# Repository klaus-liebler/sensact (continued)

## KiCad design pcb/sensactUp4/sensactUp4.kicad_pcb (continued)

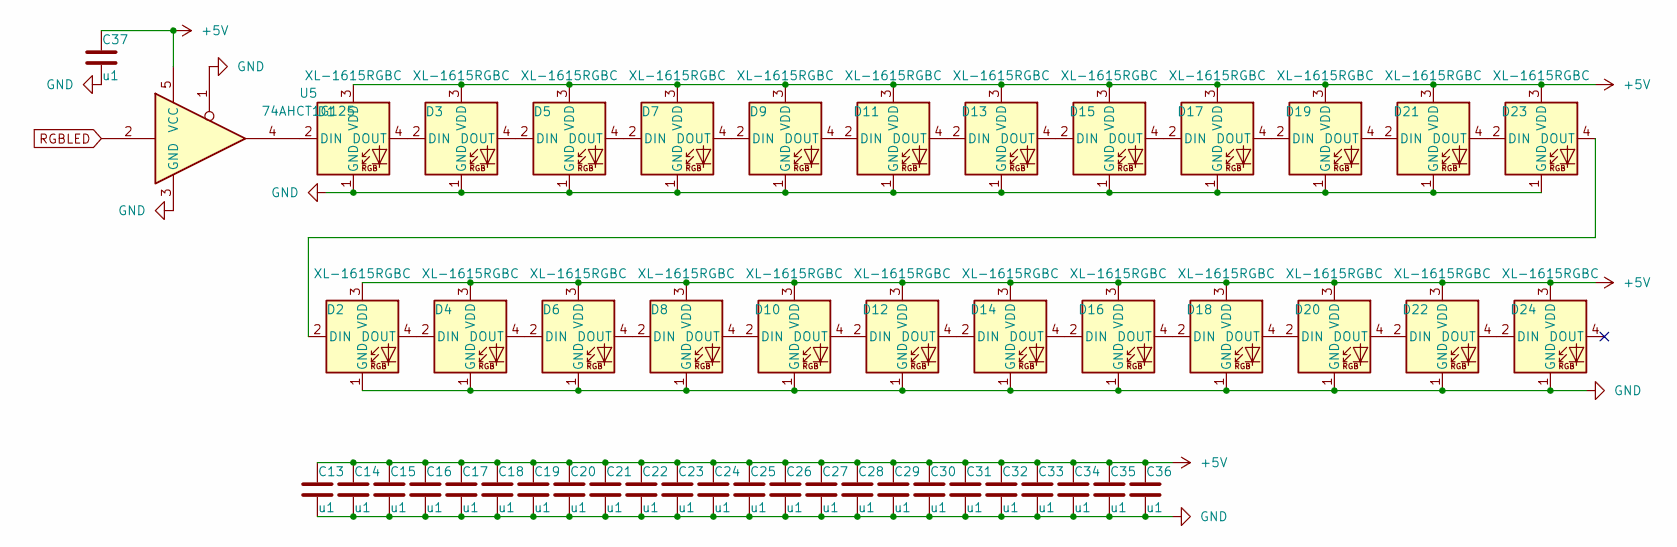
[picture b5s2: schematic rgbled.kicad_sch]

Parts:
C13, C14, C15, C16, C17, C18, C19, C20, C21, C22, C23, C24, C25, C26, C27, C28, C29, C30, C31, C32, C33, C34, C35, C36, C37: u1; C_0201_0603Metric
D1, D2, D3, D4, D5, D6, D7, D8, D9, D10, D11, D12, D13, D14, D15, D16, D17, D18, D19, D20, D21, D22, D23, D24: XL-1615RGBC; XL-1615
U5: 74AHCT1G125; SOT-23-5

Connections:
+5V: C13.1, C14.1, C15.1, C16.1, C17.1, C18.1, C19.1, C20.1, C21.1, C22.1, C23.1, C24.1, C25.1, C26.1, C27.1, C28.1, C29.1, C30.1, C31.1, C32.1, C33.1, C34.1, C35.1, C36.1, C37.1, D1.3 (VDD), D2.3 (VDD), D3.3 (VDD), D4.3 (VDD), D5.3 (VDD), D6.3 (VDD), D7.3 (VDD), D8.3 (VDD), D9.3 (VDD), D10.3 (VDD), D11.3 (VDD), D12.3 (VDD), D13.3 (VDD), D14.3 (VDD), D15.3 (VDD), D16.3 (VDD), D17.3 (VDD), D18.3 (VDD), D19.3 (VDD), D20.3 (VDD), D21.3 (VDD), D22.3 (VDD), D23.3 (VDD), D24.3 (VDD), U5.5 (VCC); also elsewhere on the board
GND: C13.2, C14.2, C15.2, C16.2, C17.2, C18.2, C19.2, C20.2, C21.2, C22.2, C23.2, C24.2, C25.2, C26.2, C27.2, C28.2, C29.2, C30.2, C31.2, C32.2, C33.2, C34.2, C35.2, C36.2, C37.2, D1.1 (GND), D2.1 (GND), D3.1 (GND), D4.1 (GND), D5.1 (GND), D6.1 (GND), D7.1 (GND), D8.1 (GND), D9.1 (GND), D10.1 (GND), D11.1 (GND), D12.1 (GND), D13.1 (GND), D14.1 (GND), D15.1 (GND), D16.1 (GND), D17.1 (GND), D18.1 (GND), D19.1 (GND), D20.1 (GND), D21.1 (GND), D22.1 (GND), D23.1 (GND), D24.1 (GND), U5.1, U5.3 (GND); also elsewhere on the board
unnamed: D1.2 (DIN), U5.4
unnamed: D1.4 (DOUT), D3.2 (DIN)
unnamed: D2.2 (DIN), D23.4 (DOUT)
unnamed: D2.4 (DOUT), D4.2 (DIN)
unnamed: D3.4 (DOUT), D5.2 (DIN)
unnamed: D4.4 (DOUT), D6.2 (DIN)
unnamed: D5.4 (DOUT), D7.2 (DIN)
unnamed: D6.4 (DOUT), D8.2 (DIN)
unnamed: D7.4 (DOUT), D9.2 (DIN)
unnamed: D8.4 (DOUT), D10.2 (DIN)
unnamed: D10.4 (DOUT), D12.2 (DIN)
unnamed: D9.4 (DOUT), D11.2 (DIN)
unnamed: D11.4 (DOUT), D13.2 (DIN)
unnamed: D12.4 (DOUT), D14.2 (DIN)
unnamed: D13.4 (DOUT), D15.2 (DIN)
unnamed: D14.4 (DOUT), D16.2 (DIN)
unnamed: D15.4 (DOUT), D17.2 (DIN)
unnamed: D16.4 (DOUT), D18.2 (DIN)
unnamed: D17.4 (DOUT), D19.2 (DIN)
unnamed: D18.4 (DOUT), D20.2 (DIN)
unnamed: D19.4 (DOUT), D21.2 (DIN)
unnamed: D20.4 (DOUT), D22.2 (DIN)
unnamed: D21.4 (DOUT), D23.2 (DIN)
unnamed: D22.4 (DOUT), D24.2 (DIN)
RGBLED: U5.2; also elsewhere on the board

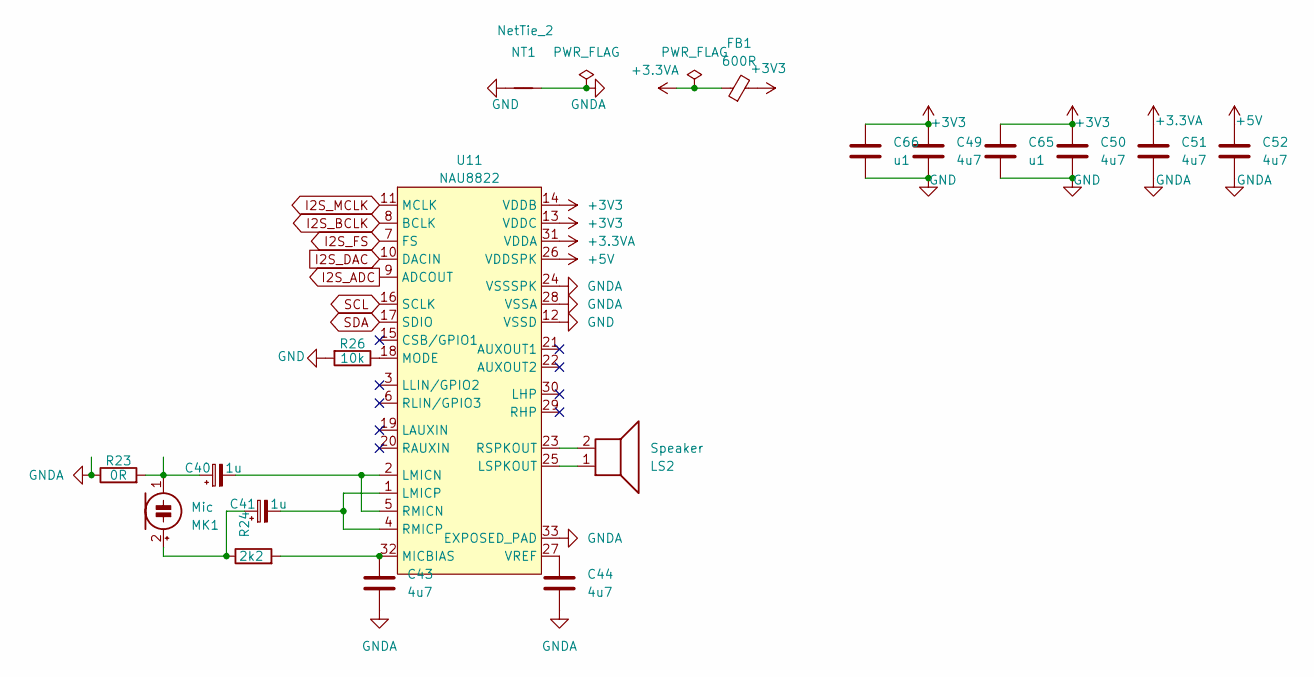
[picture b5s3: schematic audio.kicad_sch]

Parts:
C40, C41: 1u; CP_EIA-3216-10_Kemet-I; MPN TAJA105K016RNJ
C43, C44, C49, C50, C51, C52: 4u7; C_0402_1005Metric; MPN CL05A475MP5NRNC
C65, C66: u1; C_0201_0603Metric; MPN GRM033R61A104KE15D
FB1: 600R; L_0603_1608Metric; MPN BLM18AG601SN1D
LS2: Speaker; PinHeader_1x02_P1.27mm_Vertical
MK1: Mic; Microphone_6mm; MPN GMI6050P-64DB
NT1: NetTie_2; NetTie-2_SMD_Pad0.5mm
R23: 0R; R_0805_2012Metric_Pad1.20x1.40mm_HandSolder; MPN 0805W8F0000T5E
R24: 2k2; R_0402_1005Metric; MPN 0402WGF2201TCE
R26: 10k; R_0201_0603Metric; MPN 0201WMF1002TEE
U11: NAU8822; QFN-32-1EP_5x5mm_P0.5mm_EP3.6x3.6mm_ThermalVias; MPN NAU88C22YG

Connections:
+3.3VA: C51.1, FB1.1, U11.31 (VDDA)
+3V3: C49.1, C50.1, C65.1, C66.1, FB1.2, U11.13 (VDDC), U11.14 (VDDB); also elsewhere on the board
+5V: C52.1, U11.26 (VDDSPK); also elsewhere on the board
GND: C49.2, C50.2, C65.2, C66.2, NT1.1, R26.2, U11.12 (VSSD); also elsewhere on the board
GNDA: C43.2, C44.2, C51.2, C52.2, NT1.2, R23.1, U11.24 (VSSSPK), U11.28 (VSSA), U11.33 (EXPOSED_PAD)
I2S_ADC: U11.9 (ADCOUT); also elsewhere on the board
I2S_BCLK: U11.8 (BCLK); also elsewhere on the board
I2S_DAC: U11.10 (DACIN); also elsewhere on the board
I2S_FS: U11.7 (FS); also elsewhere on the board
I2S_MCLK: U11.11 (MCLK); also elsewhere on the board
unnamed: C41.1, MK1.2 (+), R24.1
unnamed: C40.1, MK1.1 (-), R23.2
unnamed: C40.2, U11.2 (LMICN), U11.5 (RMICN)
unnamed: C41.2, U11.1 (LMICP), U11.4 (RMICP)
unnamed: LS2.1, U11.25 (LSPKOUT)
unnamed: C43.1, R24.2, U11.32 (MICBIAS)
unnamed: R26.1, U11.18 (MODE)
unnamed: LS2.2, U11.23 (RSPKOUT)
unnamed: C44.1, U11.27 (VREF)
SCL: U11.16 (SCLK); also elsewhere on the board
SDA: U11.17 (SDIO); also elsewhere on the board

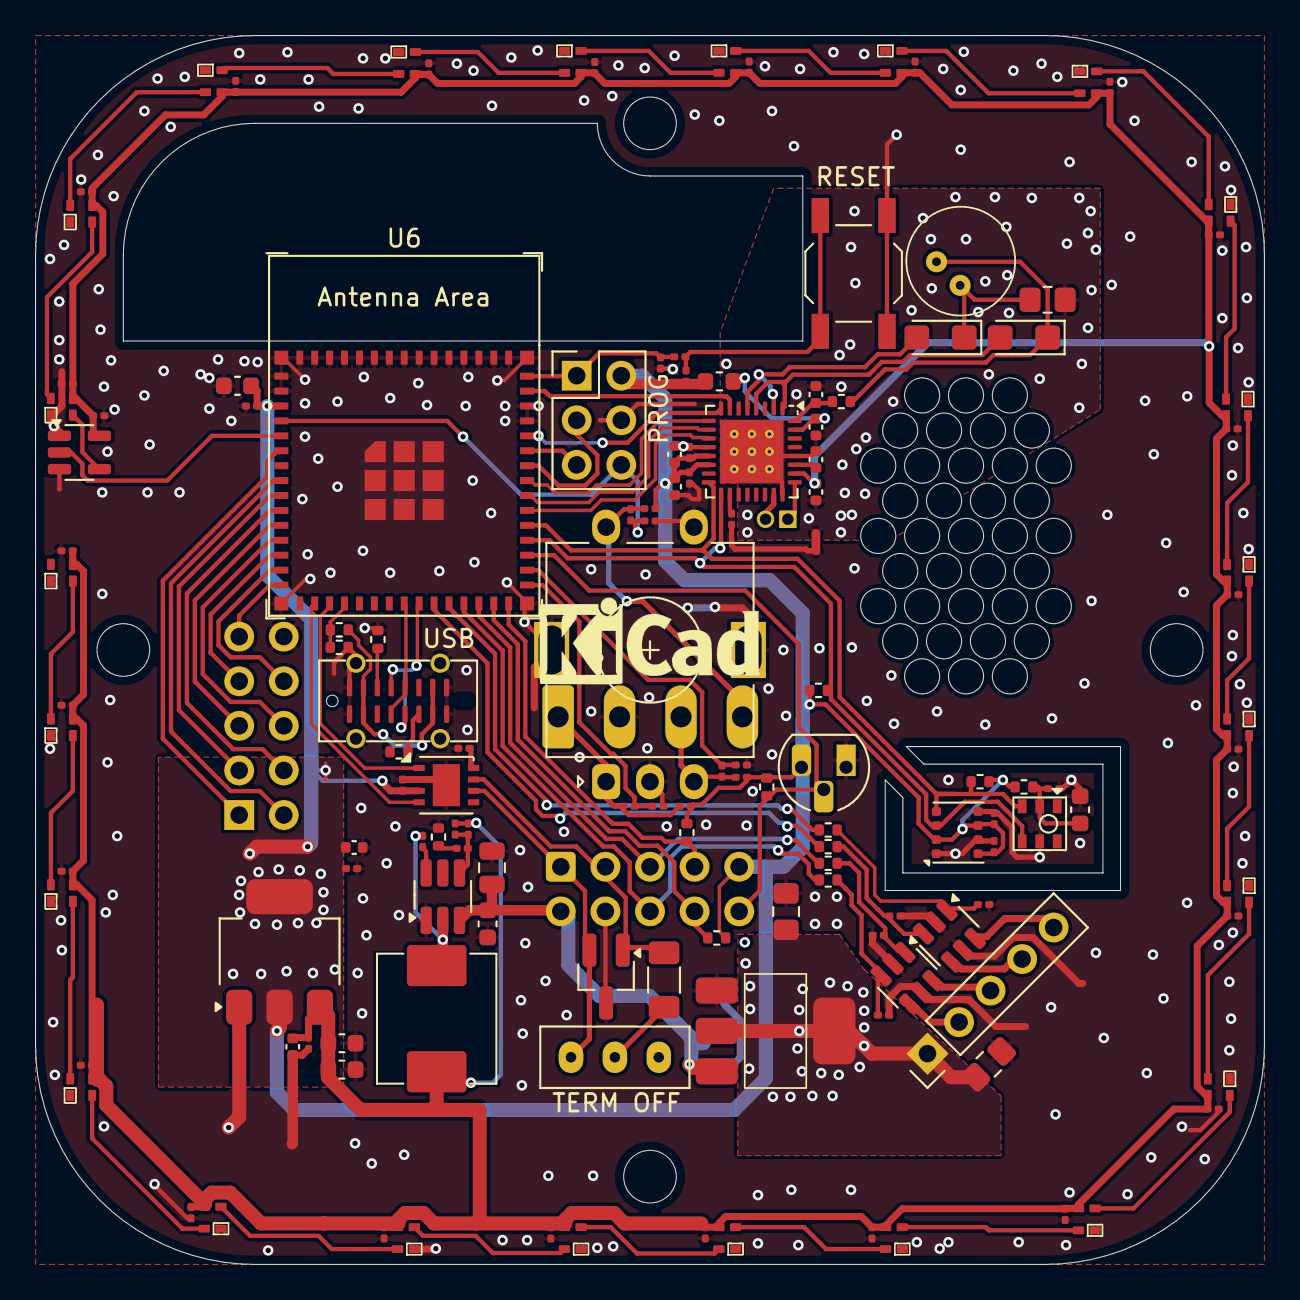
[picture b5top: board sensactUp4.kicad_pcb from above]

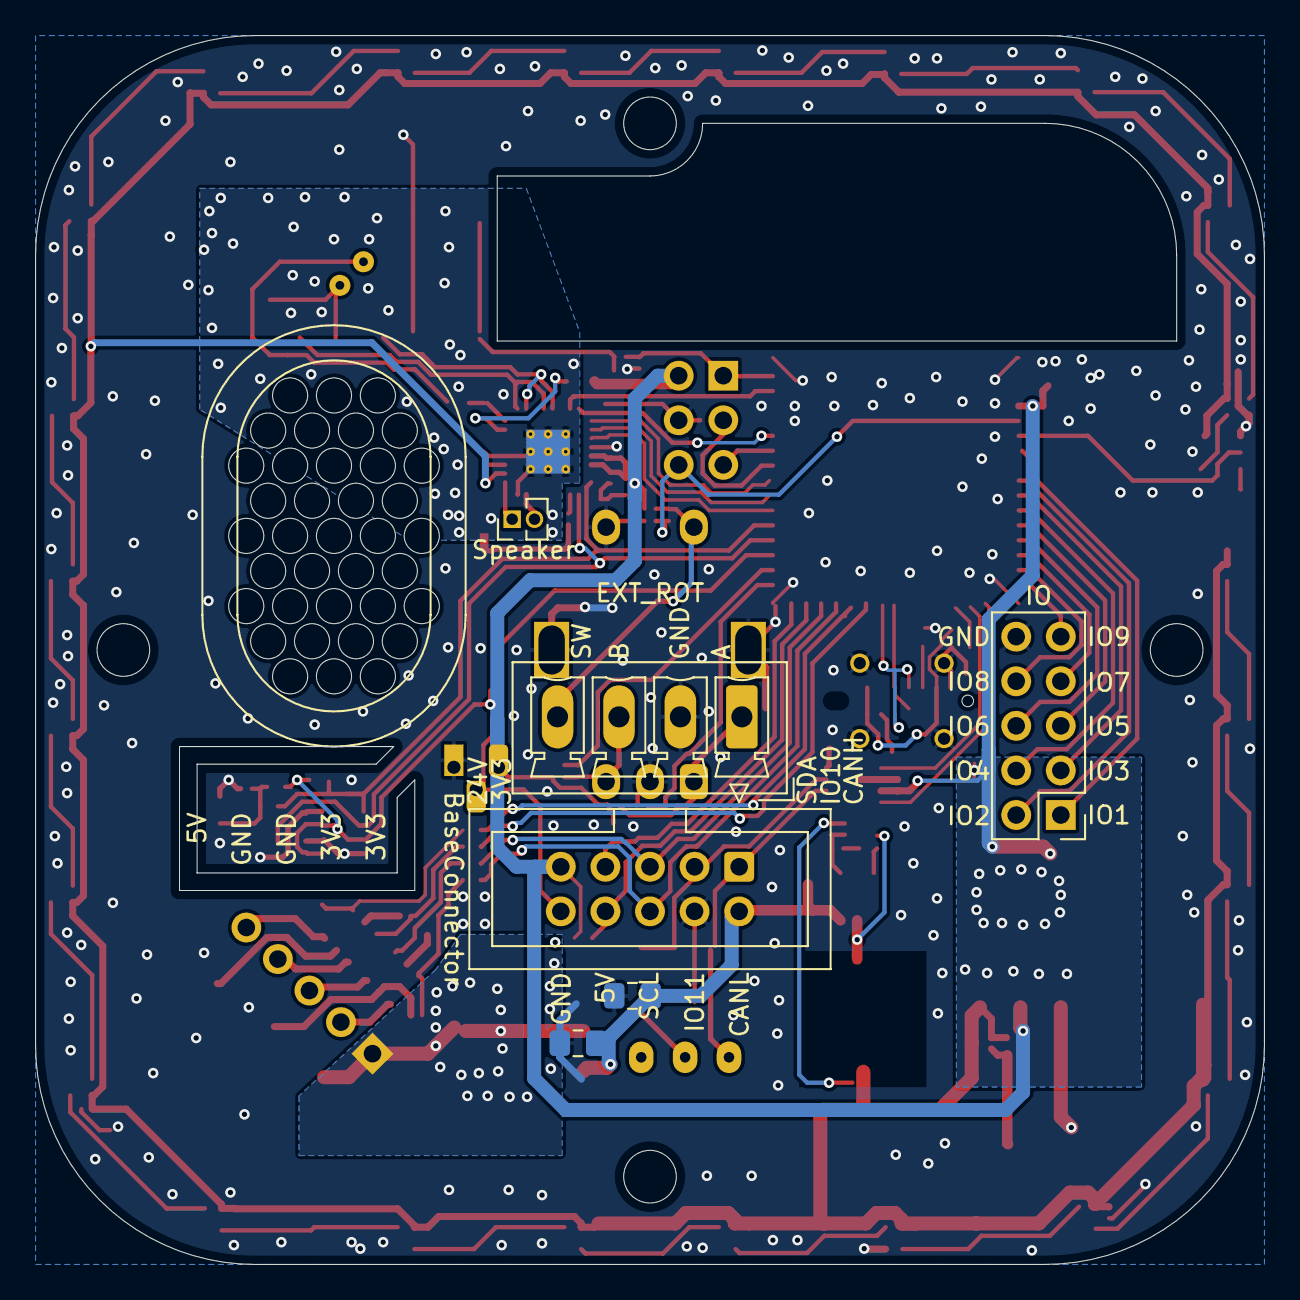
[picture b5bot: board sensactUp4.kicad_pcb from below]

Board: 2 copper layers, 70.0 x 70.0 mm, 147 parts (7 on the bottom side), 99 nets.

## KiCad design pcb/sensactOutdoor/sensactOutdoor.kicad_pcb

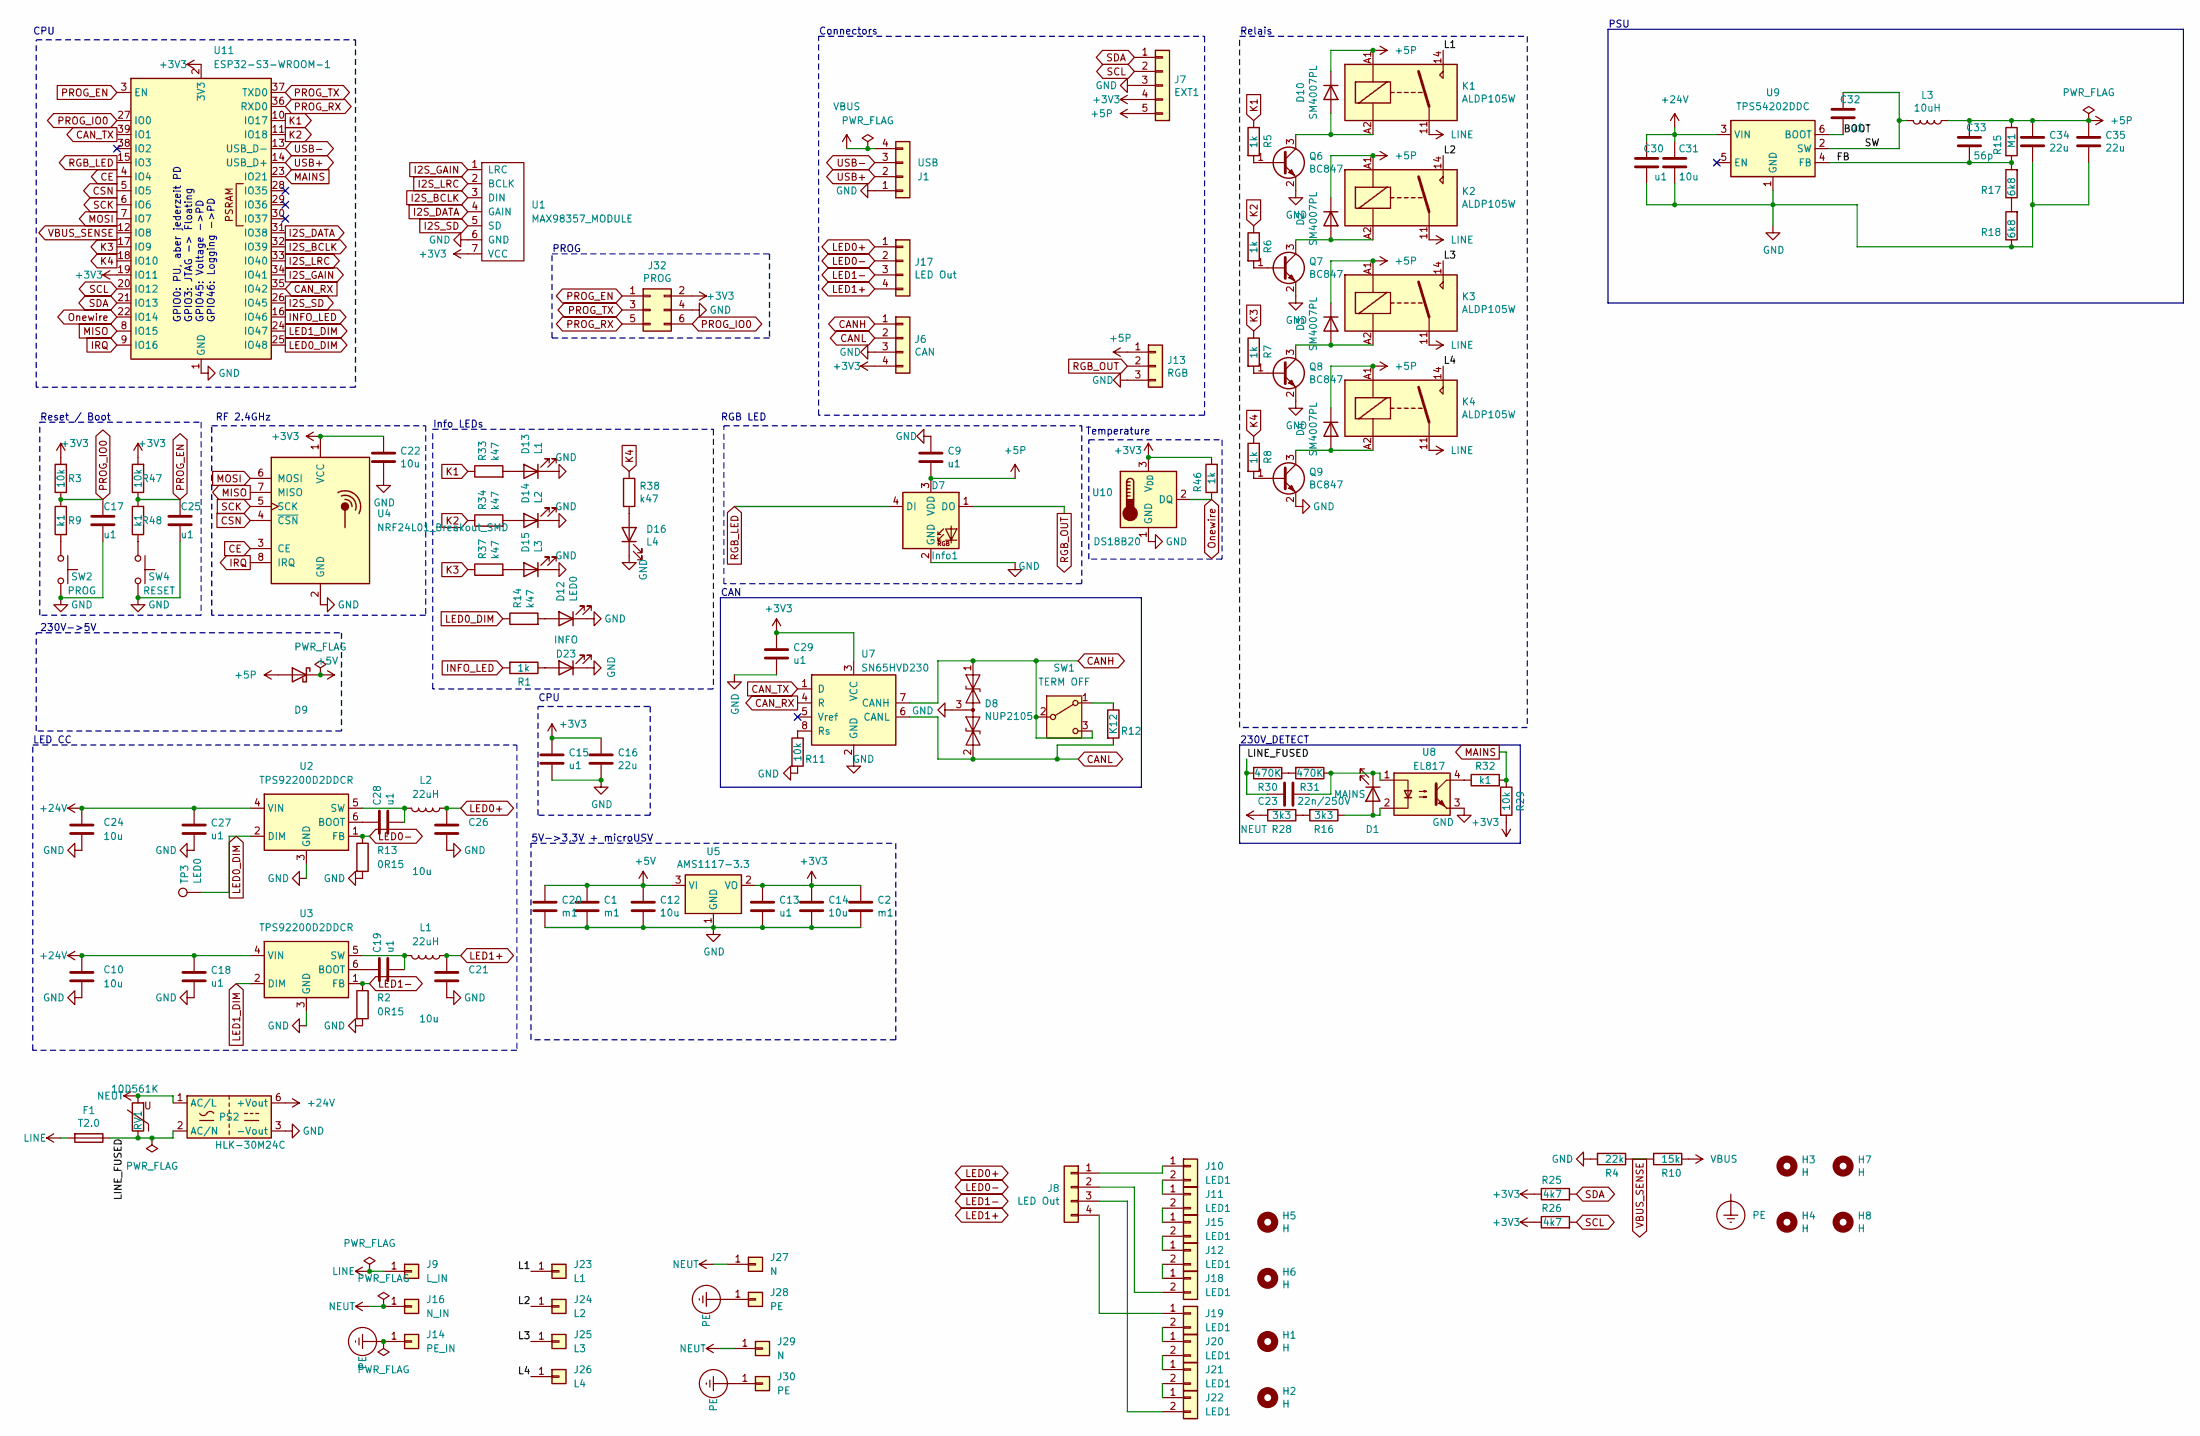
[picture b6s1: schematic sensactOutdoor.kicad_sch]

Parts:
C1, C2, C20: m1; C_1206_3216Metric; JLCPCB C15008
C9, C13, C17, C18, C19, C25, C27, C28, C30, C32: u1; C_0805_2012Metric_Pad1.18x1.45mm_HandSolder
C10, C21, C24, C26, C31: 10u; C_1206_3216Metric_Pad1.33x1.80mm_HandSolder
C12: 10u; C_0805_2012Metric_Pad1.18x1.45mm_HandSolder; JLCPCB C19702
C14, C22: 10u; C_0805_2012Metric_Pad1.18x1.45mm_HandSolder
C15: u1; C_0805_2012Metric_Pad1.18x1.45mm_HandSolder; JLCPCB C1525
C16: 22u; C_0805_2012Metric_Pad1.18x1.45mm_HandSolder; JLCPCB C59461
C23: 22n/250V; C_Rect_L11.0mm_W5.1mm_P10.00mm_MKT
C29: u1; C_0805_2012Metric; MPN GRM033R61A104KE15D
C33: 56p; C_0805_2012Metric_Pad1.18x1.45mm_HandSolder
C34, C35: 22u; C_0805_2012Metric_Pad1.18x1.45mm_HandSolder
D1: MAINS; LED_0805_2012Metric_Pad1.15x1.40mm_HandSolder
D2, D3, D4, D10: SM4007PL; D_SOD-123_handsolder; JLCPCB C64898
D7: Info1; LED_D5.0mm-4_RGB_Staggered_Pins
D8: NUP2105; SOT-23_Handsoldering; MPN NUP2105L
D9: 1N5819WS; D_SMA_Handsoldering
D12: LED0; LED_0805_2012Metric_Pad1.15x1.40mm_HandSolder; JLCPCB C2286
D13: L1; LED_0805_2012Metric_Pad1.15x1.40mm_HandSolder; JLCPCB C2286
D14: L2; LED_0805_2012Metric_Pad1.15x1.40mm_HandSolder; JLCPCB C2286
D15: L3; LED_0805_2012Metric_Pad1.15x1.40mm_HandSolder; JLCPCB C2286
D16: L4; LED_0805_2012Metric_Pad1.15x1.40mm_HandSolder; JLCPCB C2286
D23: INFO; LED_0805_2012Metric_Pad1.15x1.40mm_HandSolder
F1: T2.0; Fuse_Littelfuse_372_D8.50mm
H1, H2, H3, H4, H5, H6, H7, H8: H; MountingHole_3.2mm_M3
J1: USB; PinHeader_1x04_P2.54mm_Vertical
J6: CAN; PhoenixContact_MCV_1,5_4-G-3.5_1x04_P3.50mm_Vertical
J7: EXT1; JST_XH_B5B-XH-A_1x05_P2.50mm_Vertical
J8: LED Out; ÖLFLEX 4x1mm2
J9: L_IN; Flachstecker gewinkelt 4,8 oder 6,35mm
J10, J11, J12, J15, J18, J19, J20, J21, J22: LED1; JST_XH_B2B-XH-A_1x02_P2.50mm_Vertical
J13: RGB; PinHeader_1x03_P2.54mm_Vertical
J14: PE_IN; Flachstecker gewinkelt 4,8 oder 6,35mm
J16: N_IN; Flachstecker gewinkelt 4,8 oder 6,35mm
J17: LED Out; PhoenixContact_MCV_1,5_4-G-3.5_1x04_P3.50mm_Vertical
J23: L1; Flachstecker gewinkelt 4,8 oder 6,35mm
J24: L2; Flachstecker gewinkelt 4,8 oder 6,35mm
J25: L3; Flachstecker gewinkelt 4,8 oder 6,35mm
J26: L4; Flachstecker gewinkelt 4,8 oder 6,35mm
J27, J29: N; Flachstecker gewinkelt 4,8 oder 6,35mm
J28, J30: PE; Flachstecker gewinkelt 4,8 oder 6,35mm
J32: PROG; PinHeader_2x03_P2.54mm_Vertical
K1, K2, K3, K4: ALDP105W; RELAY_ALDP105W
L1, L2: 22uH; L_0630; JLCPCB C408455
L3: 10uH; L_0630
PS2: HLK-30M24C; Converter_ACDC_Hi-Link_HLK-30Mxx
Q6: BC847; SOT-23_Handsoldering; JLCPCB C8512
Q7, Q8, Q9: BC847; SOT-23_Handsoldering
R1, R5, R6, R7, R8, R46: 1k; R_0805_2012Metric_Pad1.20x1.40mm_HandSolder
R2, R13: 0R15; R_1206_3216Metric_Pad1.30x1.75mm_HandSolder; JLCPCB C25271
R3, R29, R47: 10k; R_0805_2012Metric_Pad1.20x1.40mm_HandSolder
R4: 22k; R_0805_2012Metric_Pad1.20x1.40mm_HandSolder
R9, R32, R48: k1; R_0805_2012Metric_Pad1.20x1.40mm_HandSolder
R10: 15k; R_0805_2012Metric_Pad1.20x1.40mm_HandSolder
R11: 10k; R_0805_2012Metric_Pad1.20x1.40mm_HandSolder; MPN 0201WMF1002TEE
R12: K12; R_1206_3216Metric_Pad1.30x1.75mm_HandSolder; MPN 1206W4F1200T5E
R14, R33, R34, R37, R38: k47; R_0805_2012Metric_Pad1.20x1.40mm_HandSolder
R15: M1; R_0805_2012Metric_Pad1.20x1.40mm_HandSolder
R16, R28: 3k3; R_2512_6332Metric_Pad1.40x3.35mm_HandSolder
R17, R18: 6k8; R_0805_2012Metric_Pad1.20x1.40mm_HandSolder
R25, R26: 4k7; R_0805_2012Metric_Pad1.20x1.40mm_HandSolder
R30, R31: 470K; R_2512_6332Metric_Pad1.40x3.35mm_HandSolder
RV1: 10D561K; RV_Disc_D12mm_W3.9mm_P7.5mm
SW1: TERM OFF; Switch_SS12D00
SW2: PROG; SW_SPST_TL3342_smaller_handsolder
SW4: RESET; SW_SPST_TL3342_smaller_handsolder
TP3: LED0; TestPoint_THTPad_D2.0mm_Drill1.0mm
U1: MAX98357_MODULE; PinHeader_1x07_P2.54mm_Vertical
U2, U3: TPS92200D2DDCR; SOT-23-6_Handsoldering
U4: NRF24L01_Breakout_SMD; NRF24L01-Module-SMD
U5: AMS1117-3.3; SOT-223-3_TabPin2_HANDSOLDER
U7: SN65HVD230; SOIC-8_3.9x4.9mm_Pitch1.27mm_handsolder; MPN SN65HVD230DR
U8: EL817; SO-4_7.6x3.6mm_P2.54mm_handsolder
U9: TPS54202DDC; SOT-23-6_Handsoldering
U10: DS18B20; TO-92L_HandSolder
U11: ESP32-S3-WROOM-1; ESP32-S3-WROOM-1_handsolder

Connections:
+3V3: C2.1, C13.1, C14.1, C15.1, C16.1, C22.1, C29.1, J6.4, J7.4, J32.2, R3.2, R25.1, R26.1, R29.2, R46.2, R47.2, U1.7 (VCC), U4.1 (VCC), U5.2 (VO), U7.3 (VCC), U10.3 (V_{DD}), U11.2 (3V3), U11.19 (IO11)
+5P: C9.2, C33.2, C34.1, C35.1, D2.1 (K), D3.1 (K), D4.1 (K), D7.3 (VDD), D9.2 (A), D10.1 (K), J7.5, J13.1, K1.A1, K2.A1, K3.A1, K4.A1, L3.1, R15.1
+5V: C1.1, C12.1, C20.1, D9.1 (K), U5.3 (VI)
+24V: C10.1, C18.1, C24.1, C27.1, C30.2, C31.2, PS2.6 (+Vout), U2.4 (VIN), U3.4 (VIN), U9.3 (VIN)
/BOOT: C32.1, U9.6 (BOOT)
/FB: C33.1, R15.2, R17.2, U9.4 (FB)
/L1: J23.1, K1.14
/L2: J24.1, K2.14
/L3: J25.1, K3.14
/L4: J26.1, K4.14
/LINE_FUSED: C23.1, F1.1, PS2.2 (AC/N), R30.2, RV1.1
/SW: C32.2, L3.2, U9.2 (SW)
CANH: D8.1 (A1), J6.1, SW1.2 (B), SW1.3 (C), U7.7 (CANH)
CANL: D8.2 (A2), J6.2, R12.2, U7.6 (CANL)
CAN_RX: U7.4 (R), U11.35 (IO42)
CAN_TX: U7.1 (D), U11.39 (IO1)
CE: U4.3 (CE), U11.4 (IO4)
CSN: U4.4 (~CSN), U11.5 (IO5)
GND: C1.2, C2.2, C9.1, C10.2, C12.2, C13.2, C14.2, C15.2, C16.2, C17.2, C18.2, C20.2, C21.2, C22.2, C24.2, C25.2, C26.2, C27.2, C29.2, C30.1, C31.1, C34.2, C35.2, D7.2 (GND), D8.3 (common), D12.1 (K), D13.1 (K), D14.1 (K), D15.1 (K), D16.1 (K), D23.1 (K), J1.1, J6.3, J7.3, J13.3, J32.4, PS2.3 (-Vout), Q6.2 (E), Q7.2 (E), Q8.2 (E), Q9.2 (E), R2.2, R4.2, R11.2, R13.2, R18.1, SW2.2, SW4.2, U1.6 (GND), U2.3 (GND), U3.3 (GND), U4.2 (GND), U5.1 (GND), U7.2 (GND), U8.3, U9.1 (GND), U10.1 (GND), U11.1 (GND), U11.40 (GND), U11.41 (GND)
I2S_BCLK: U1.3 (DIN), U11.32 (IO39)
I2S_DATA: U1.4 (GAIN), U11.31 (IO38)
I2S_GAIN: U1.1 (LRC), U11.34 (IO41)
I2S_LRC: U1.2 (BCLK), U11.33 (IO40)
I2S_SD: U1.5 (SD), U11.26 (IO45)
INFO_LED: R1.2, U11.16 (IO46)
IRQ: U4.8 (IRQ), U11.9 (IO16)
K1: R5.1, R33.1, U11.10 (IO17)
K2: R6.1, R34.1, U11.11 (IO18)
K3: R7.1, R37.1, U11.17 (IO9)
K4: R8.1, R38.1, U11.18 (IO10)
LED0+: C26.1, J17.1, L2.1
LED0-: J17.2, R13.1, U2.1 (FB)
LED0_DIM: R14.1, TP3.1, U2.2 (DIM), U11.25 (IO48)
LED1+: C21.1, J17.4, L1.1
LED1-: J17.3, R2.1, U3.1 (FB)
LED1_DIM: U3.2 (DIM), U11.24 (IO47)
LINE: F1.2, J9.1, K1.11, K2.11, K3.11, K4.11
MAINS: R29.1, R32.2, U11.23 (IO21)
MISO: U4.7 (MISO), U11.8 (IO15)
MOSI: U4.6 (MOSI), U11.7 (IO7)
NEUT: J16.1, J27.1, J29.1, PS2.1 (AC/L), R28.2, RV1.2
unnamed: D1.2 (A), R16.1, U8.2
unnamed: C23.2, D1.1 (K), R31.1, U8.1
unnamed: D2.2 (A), K2.A2, Q7.3 (C)
unnamed: D3.2 (A), K3.A2, Q8.3 (C)
unnamed: D4.2 (A), K4.A2, Q9.3 (C)
unnamed: D10.2 (A), K1.A2, Q6.3 (C)
unnamed: D12.2 (A), R14.2
unnamed: D13.2 (A), R33.2
unnamed: D14.2 (A), R34.2
unnamed: D15.2 (A), R37.2
unnamed: D16.2 (A), R38.2
unnamed: D23.2 (A), R1.1
unnamed: J8.1, J10.1
unnamed: J10.2, J11.1
unnamed: J11.2, J15.1
unnamed: J12.1, J15.2
unnamed: J12.2, J18.1
unnamed: J8.2, J18.2
unnamed: J8.4, J19.1
unnamed: J19.2, J20.1
unnamed: J20.2, J21.1
unnamed: J21.2, J22.1
unnamed: J8.3, J22.2
unnamed: Q6.1 (B), R5.2
unnamed: Q7.1 (B), R6.2
unnamed: Q8.1 (B), R7.2
unnamed: Q9.1 (B), R8.2
unnamed: R9.1, SW2.1
unnamed: R16.2, R28.1
unnamed: R17.1, R18.2
unnamed: R30.1, R31.2
unnamed: R32.1, U8.4
unnamed: R48.1, SW4.1
unnamed: R12.1, SW1.1 (A)
unnamed: C28.1, U2.6 (BOOT)
unnamed: C28.2, L2.2, U2.5 (SW)
unnamed: C19.1, U3.6 (BOOT)
unnamed: C19.2, L1.2, U3.5 (SW)
unnamed: R11.1, U7.8 (Rs)
Onewire: R46.1, U10.2 (DQ), U11.22 (IO14)
PE: J14.1, J28.1, J30.1
PROG_EN: C25.1, J32.1, R47.1, R48.2, U11.3 (EN)
PROG_IO0: C17.1, J32.6, R3.1, R9.2, U11.27 (IO0)
PROG_RX: J32.5, U11.36 (RXD0)
PROG_TX: J32.3, U11.37 (TXD0)
RGB_LED: D7.4 (DI), U11.15 (IO3)
RGB_OUT: D7.1 (DO), J13.2
SCK: U4.5 (SCK), U11.6 (IO6)
SCL: J7.2, R26.2, U11.20 (IO12)
SDA: J7.1, R25.2, U11.21 (IO13)
USB+: J1.2, U11.14 (USB_D+)
USB-: J1.3, U11.13 (USB_D-)
VBUS: J1.4, R10.1
VBUS_SENSE: R4.1, R10.2, U11.12 (IO8)

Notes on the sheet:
230V->5V
Relais
CPU
Temperature
LED CC
PSU
RF 2.4GHz
Connectors
CAN
230V_DETECT
Info LEDs
Reset / Boot
RGB LED
PROG
5V->3,3V + microUSV
GPIO0: PU, aber jederzeit PD GPIO3: JTAG -> Floating GPIO45: Voltage ->PD GPIO46: Logging ->PD

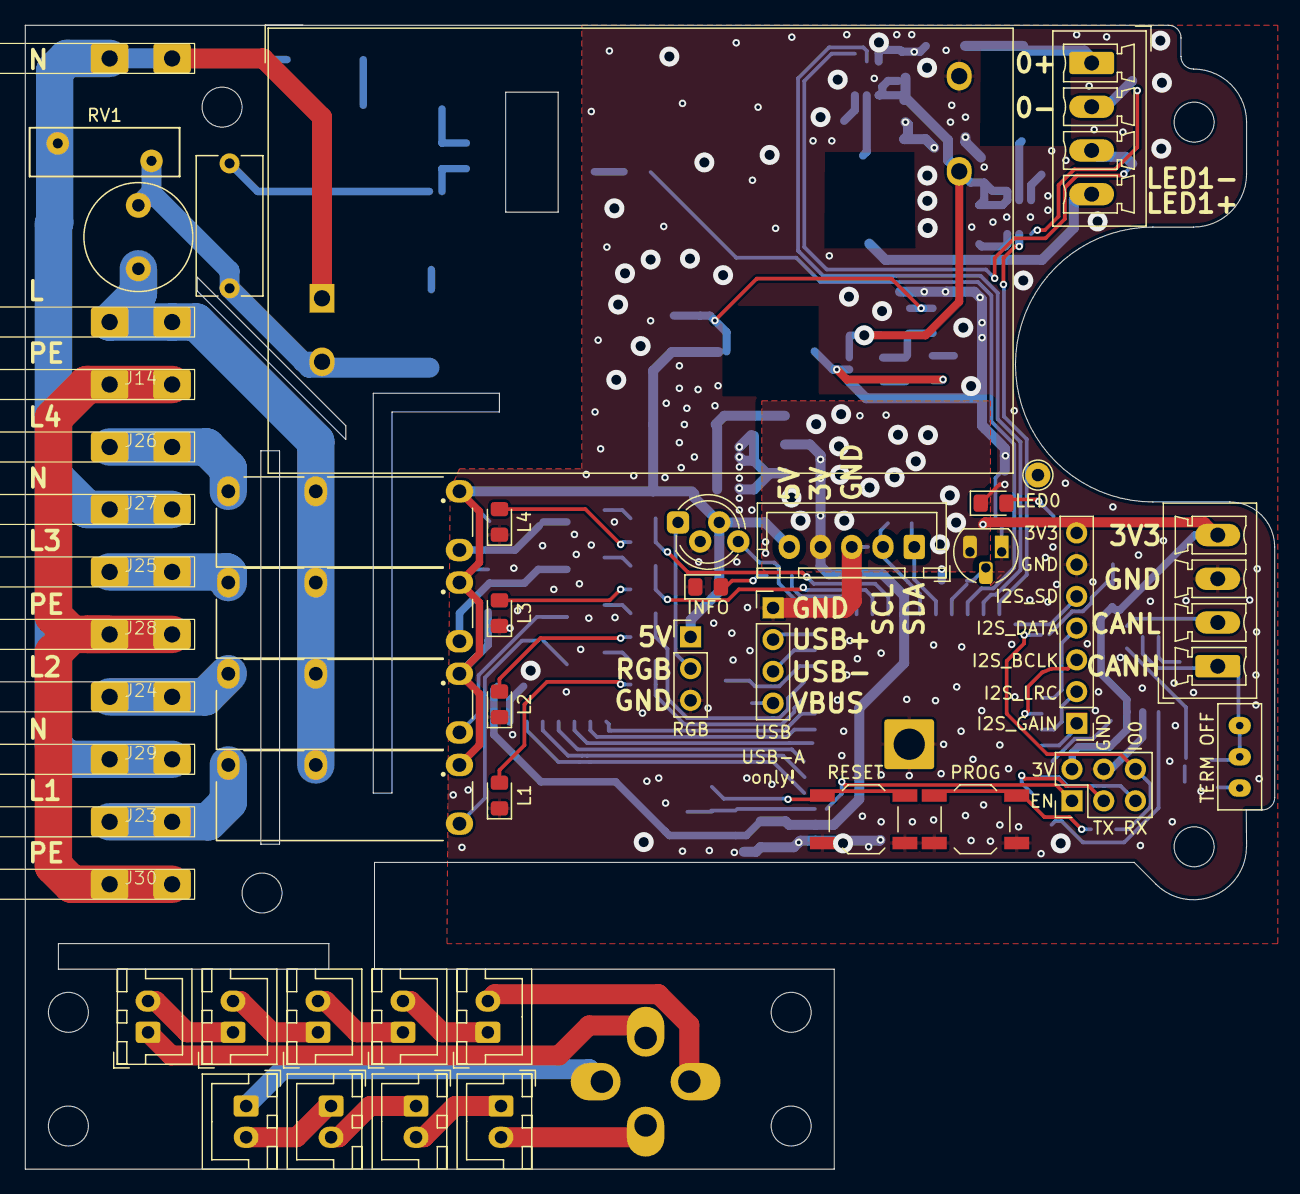
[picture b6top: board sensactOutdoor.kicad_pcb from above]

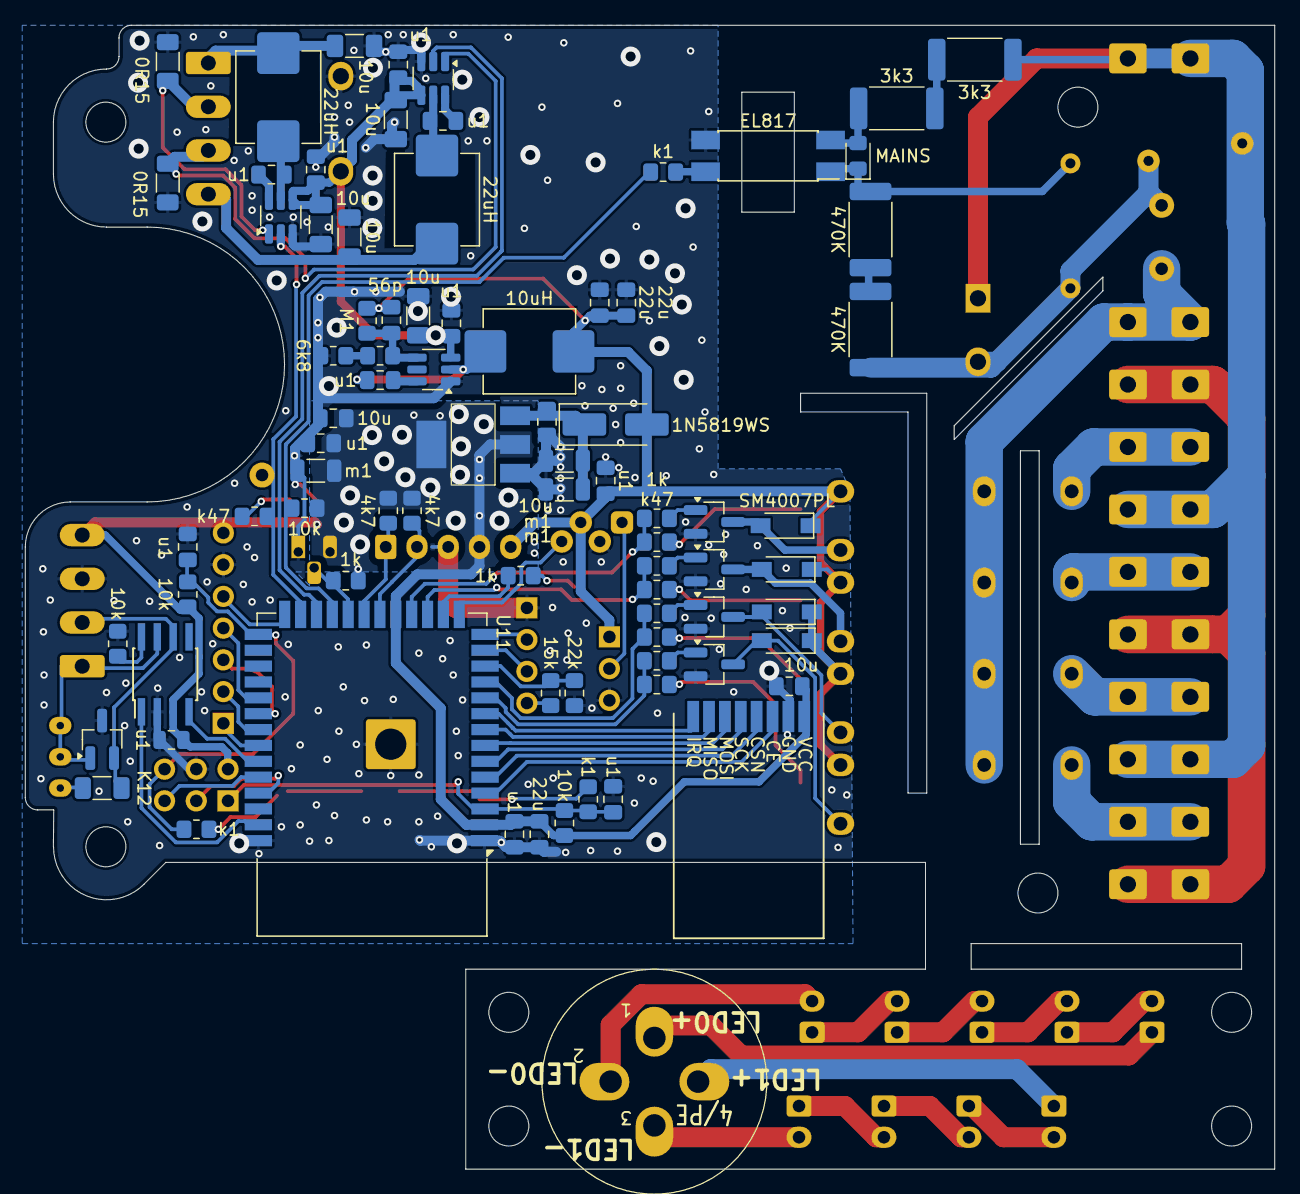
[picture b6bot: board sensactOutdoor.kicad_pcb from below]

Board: 2 copper layers, 100.0 x 91.6 mm, 137 parts (82 on the bottom side), 95 nets.

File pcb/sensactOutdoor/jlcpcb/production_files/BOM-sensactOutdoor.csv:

Comment,Designator,Footprint,LCSC,Quantity
m1,"C1,C2,C20",C_1206_3216Metric,C15008,3
u1,C15,C_0805_2012Metric_Pad1.18x1.45mm_HandSolder,C1525,1
10u,C12,C_0805_2012Metric_Pad1.18x1.45mm_HandSolder,C19702,1
LED0,"D12,D13,D14,D15,D16",LED_0805_2012Metric_Pad1.15x1.40mm_HandSolder,C2286,5
0R15,"R13,R2",R_1206_3216Metric_Pad1.30x1.75mm_HandSolder,C25271,2
22uH,"L1,L2",L_0630,C408455,2
u1,"C13,C17,C18,C19,C25,C27,C28,C30,C32,C9",C_0805_2012Metric_Pad1.18x1.45mm_HandSolder,C49678,10
22u,C16,C_0805_2012Metric_Pad1.18x1.45mm_HandSolder,C59461,1
SM4007PL,"D10,D2,D3,D4",D_SOD-123_handsolder,C64898,4
BC847,Q6,SOT-23_Handsoldering,C8512,1
LED1,J22,JST_XH_B2B-XH-A_1x02_P2.50mm_Vertical,,1
H,H6,MountingHole_3.2mm_M3,,1
L1,J23,"Flachstecker gewinkelt 4,8 oder 6,35mm",,1
LED1,J15,JST_XH_B2B-XH-A_1x02_P2.50mm_Vertical,,1
ALDP105W,K1,RELAY_ALDP105W,,1
H,H1,MountingHole_3.2mm_M3,,1
LED1,J10,JST_XH_B2B-XH-A_1x02_P2.50mm_Vertical,,1
N,J29,"Flachstecker gewinkelt 4,8 oder 6,35mm",,1
LED Out,J17,"PhoenixContact_MCV_1,5_4-G-3.5_1x04_P3.50mm_Vertical",,1
H,H5,MountingHole_3.2mm_M3,,1
INFO,D23,LED_0805_2012Metric_Pad1.15x1.40mm_HandSolder,,1
RGB,J13,PinHeader_1x03_P2.54mm_Vertical,,1
DS18B20,U10,TO-92L_HandSolder,,1
LED1,J19,JST_XH_B2B-XH-A_1x02_P2.50mm_Vertical,,1
LED0,TP3,TestPoint_THTPad_D2.0mm_Drill1.0mm,,1
10D561K,RV1,RV_Disc_D12mm_W3.9mm_P7.5mm,,1
N,J27,"Flachstecker gewinkelt 4,8 oder 6,35mm",,1
L_IN,J9,"Flachstecker gewinkelt 4,8 oder 6,35mm",,1
T2.0,F1,Fuse_Littelfuse_372_D8.50mm,,1
MAX98357_MODULE,U1,PinHeader_1x07_P2.54mm_Vertical,,1
LED1,J12,JST_XH_B2B-XH-A_1x02_P2.50mm_Vertical,,1
PE,J28,"Flachstecker gewinkelt 4,8 oder 6,35mm",,1
H,H8,MountingHole_3.2mm_M3,,1
L3,J25,"Flachstecker gewinkelt 4,8 oder 6,35mm",,1
ALDP105W,K2,RELAY_ALDP105W,,1
N_IN,J16,"Flachstecker gewinkelt 4,8 oder 6,35mm",,1
LED1,J11,JST_XH_B2B-XH-A_1x02_P2.50mm_Vertical,,1
PROG,SW2,SW_SPST_TL3342_smaller_handsolder,,1
LED1,J20,JST_XH_B2B-XH-A_1x02_P2.50mm_Vertical,,1
USB,J1,PinHeader_1x04_P2.54mm_Vertical,,1
22n/250V,C23,C_Rect_L11.0mm_W5.1mm_P10.00mm_MKT,,1
H,H3,MountingHole_3.2mm_M3,,1
TERM OFF,SW1,Switch_SS12D00,,1
PROG,J32,PinHeader_2x03_P2.54mm_Vertical,,1
ALDP105W,K4,RELAY_ALDP105W,,1
RESET,SW4,SW_SPST_TL3342_smaller_handsolder,,1
L4,J26,"Flachstecker gewinkelt 4,8 oder 6,35mm",,1
HLK-30M24C,PS2,Converter_ACDC_Hi-Link_HLK-30Mxx,,1
LED1,J18,JST_XH_B2B-XH-A_1x02_P2.50mm_Vertical,,1
PE,J30,"Flachstecker gewinkelt 4,8 oder 6,35mm",,1
H,H2,MountingHole_3.2mm_M3,,1
ALDP105W,K3,RELAY_ALDP105W,,1
Info1,D7,LED_D5.0mm-4_RGB_Staggered_Pins,,1
LED1,J21,JST_XH_B2B-XH-A_1x02_P2.50mm_Vertical,,1
H,H4,MountingHole_3.2mm_M3,,1
PE_IN,J14,"Flachstecker gewinkelt 4,8 oder 6,35mm",,1
EXT1,J7,JST_XH_B5B-XH-A_1x05_P2.50mm_Vertical,,1
L2,J24,"Flachstecker gewinkelt 4,8 oder 6,35mm",,1
CAN,J6,"PhoenixContact_MCV_1,5_4-G-3.5_1x04_P3.50mm_Vertical",,1
H,H7,MountingHole_3.2mm_M3,,1
1k,R7,R_0805_2012Metric_Pad1.20x1.40mm_HandSolder,,1
MAINS,D1,LED_0805_2012Metric_Pad1.15x1.40mm_HandSolder,,1
LED Out,J8,ÖLFLEX 4x1mm2,,1
AMS1117-3.3,U5,SOT-223-3_TabPin2_HANDSOLDER,,1
470K,R31,R_2512_6332Metric_Pad1.40x3.35mm_HandSolder,,1
1k,R1,R_0805_2012Metric_Pad1.20x1.40mm_HandSolder,,1
3k3,R16,R_2512_6332Metric_Pad1.40x3.35mm_HandSolder,,1
470K,R30,R_2512_6332Metric_Pad1.40x3.35mm_HandSolder,,1
15k,R10,R_0805_2012Metric_Pad1.20x1.40mm_HandSolder,,1
10u,C21,C_1206_3216Metric_Pad1.33x1.80mm_HandSolder,,1
k1,R32,R_0805_2012Metric_Pad1.20x1.40mm_HandSolder,,1
NUP2105,D8,SOT-23_Handsoldering,,1
BC847,Q7,SOT-23_Handsoldering,,1
BC847,Q9,SOT-23_Handsoldering,,1
K12,R12,R_1206_3216Metric_Pad1.30x1.75mm_HandSolder,,1
10uH,L3,L_0630,,1
10u,C22,C_0805_2012Metric_Pad1.18x1.45mm_HandSolder,,1
10u,C31,C_1206_3216Metric_Pad1.33x1.80mm_HandSolder,,1
TPS92200D2DDCR,U2,SOT-23-6_Handsoldering,,1
1k,R8,R_0805_2012Metric_Pad1.20x1.40mm_HandSolder,,1
4k7,R25,R_0805_2012Metric_Pad1.20x1.40mm_HandSolder,,1
6k8,R17,R_0805_2012Metric_Pad1.20x1.40mm_HandSolder,,1
10k,R3,R_0805_2012Metric_Pad1.20x1.40mm_HandSolder,,1
TPS54202DDC,U9,SOT-23-6_Handsoldering,,1
TPS92200D2DDCR,U3,SOT-23-6_Handsoldering,,1
k47,R38,R_0805_2012Metric_Pad1.20x1.40mm_HandSolder,,1
3k3,R28,R_2512_6332Metric_Pad1.40x3.35mm_HandSolder,,1
10u,C24,C_1206_3216Metric_Pad1.33x1.80mm_HandSolder,,1
k47,R34,R_0805_2012Metric_Pad1.20x1.40mm_HandSolder,,1
1N5819WS,D9,D_SMA_Handsoldering,,1
10k,R47,R_0805_2012Metric_Pad1.20x1.40mm_HandSolder,,1
k47,R33,R_0805_2012Metric_Pad1.20x1.40mm_HandSolder,,1
10k,R11,R_0805_2012Metric_Pad1.20x1.40mm_HandSolder,,1
k1,R9,R_0805_2012Metric_Pad1.20x1.40mm_HandSolder,,1
10u,C26,C_1206_3216Metric_Pad1.33x1.80mm_HandSolder,,1
k1,R48,R_0805_2012Metric_Pad1.20x1.40mm_HandSolder,,1
SN65HVD230,U7,SOIC-8_3.9x4.9mm_Pitch1.27mm_handsolder,,1
10u,C14,C_0805_2012Metric_Pad1.18x1.45mm_HandSolder,,1
22u,C34,C_0805_2012Metric_Pad1.18x1.45mm_HandSolder,,1
4k7,R26,R_0805_2012Metric_Pad1.20x1.40mm_HandSolder,,1
10k,R29,R_0805_2012Metric_Pad1.20x1.40mm_HandSolder,,1
22u,C35,C_0805_2012Metric_Pad1.18x1.45mm_HandSolder,,1
22k,R4,R_0805_2012Metric_Pad1.20x1.40mm_HandSolder,,1
k47,R14,R_0805_2012Metric_Pad1.20x1.40mm_HandSolder,,1
BC847,Q8,SOT-23_Handsoldering,,1
10u,C10,C_1206_3216Metric_Pad1.33x1.80mm_HandSolder,,1
EL817,U8,SO-4_7.6x3.6mm_P2.54mm_handsolder,,1
M1,R15,R_0805_2012Metric_Pad1.20x1.40mm_HandSolder,,1
1k,R5,R_0805_2012Metric_Pad1.20x1.40mm_HandSolder,,1
1k,R6,R_0805_2012Metric_Pad1.20x1.40mm_HandSolder,,1
56p,C33,C_0805_2012Metric_Pad1.18x1.45mm_HandSolder,,1
6k8,R18,R_0805_2012Metric_Pad1.20x1.40mm_HandSolder,,1
1k,R46,R_0805_2012Metric_Pad1.20x1.40mm_HandSolder,,1
u1,C29,C_0805_2012Metric,,1
ESP32-S3-WROOM-1,U11,ESP32-S3-WROOM-1_handsolder,,1
k47,R37,R_0805_2012Metric_Pad1.20x1.40mm_HandSolder,,1
NRF24L01_Breakout_SMD,U4,NRF24L01-Module-SMD,,1
